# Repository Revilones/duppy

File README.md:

# duppy
This is a test readme
Sense Everything

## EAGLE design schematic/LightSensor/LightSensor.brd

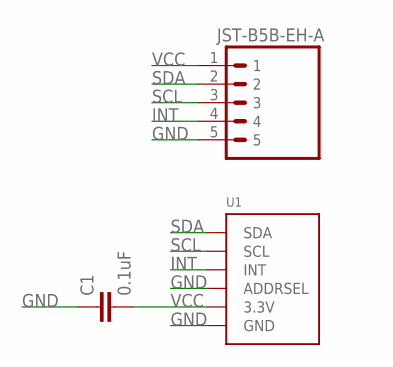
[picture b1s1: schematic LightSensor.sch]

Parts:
C1: 0.1uF; 0603-CAP
U1: LIGHT_TSL2561; TSL2561_FN
U$1: JST-B5B-EH-A; JST-B5B-ED-A

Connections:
GND: C1.1, U1.ADR (ADDRSEL), U1.VSS (GND), U$1.5
INT: U1.INT, U$1.4
SCL: U1.CLK (SCL), U$1.3
SDA: U1.DATA (SDA), U$1.2
VCC: C1.2, U1.VDD (3.3V), U$1.1

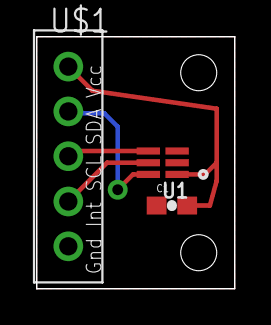
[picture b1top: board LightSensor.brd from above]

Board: 2 copper layers, 11.0 x 14.0 mm, 3 parts (0 on the bottom side), 5 nets.

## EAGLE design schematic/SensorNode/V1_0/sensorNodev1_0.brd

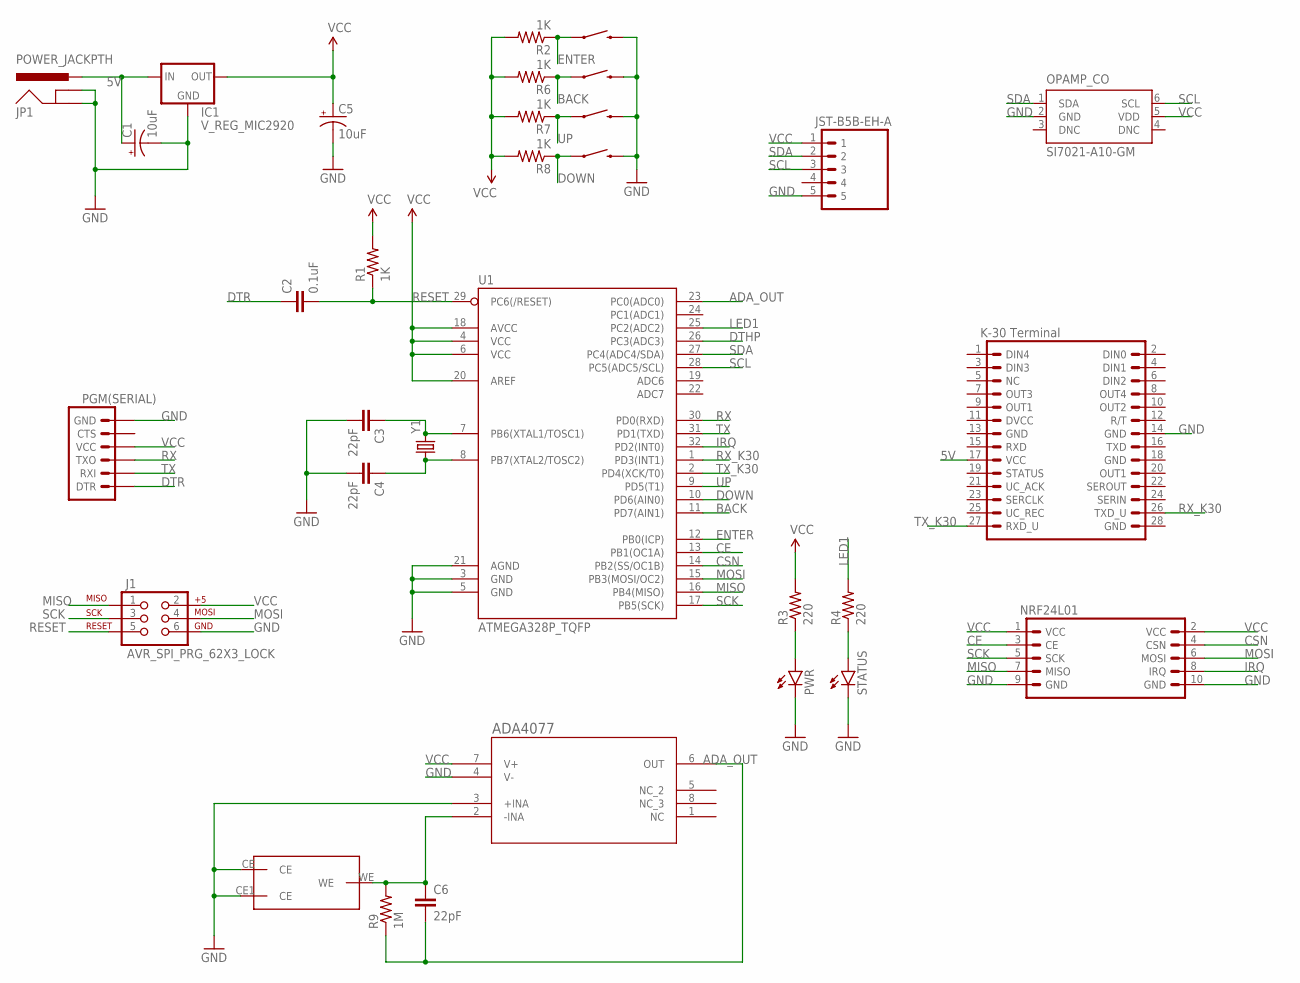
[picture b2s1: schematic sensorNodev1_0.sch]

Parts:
BACK: SWITCH-MOMENTARY-2PTH; TACTILE-PTH
C1, C5: 10uF; CPOL-RADIAL-10UF-25V
C2: 0.1uF; 0603-CAP
C3, C4, C6: 22pF; 0603-CAP
CO2: K-30K-30; K-30
DOWN: SWITCH-MOMENTARY-2PTH; TACTILE-PTH
ENTER: SWITCH-MOMENTARY-2PTH; TACTILE-PTH
IC1: V_REG_MIC2920; SOT223
J1: AVR_SPI_PRG_62X3_LOCK; 2X3_LOCK
JP1: POWER_JACKPTH; POWER_JACK_PTH
OPAMP_CO: SI7021-A10-GM; DFN6-3X3
PGM(SERIAL): ARDUINO_SERIAL_PROGRAMPTH; 1X06
PWR: LED0603; LED-0603
R1, R2, R6, R7, R8: 1K; 0603-RES
R3, R4: 220; 0603-RES
R9: 1M; 0603-RES
SCREEN: JST-B5B-EH-A; JST-B5B-ED-A
STATUS: LED0603; LED-0603
U1: ATMEGA328P_TQFP; TQFP32-08
U2: ADA4077-1ARZ; R_8
U$1: TGS5042A; TGS5042
U$2: NRF24L01
UP: SWITCH-MOMENTARY-2PTH; TACTILE-PTH
Y1: CRYSTALHC49US; HC49US

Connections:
5V: C1.1 (+), CO2.17 (VCC), IC1.1 (IN), JP1.PWR
ADA_OUT: C6.2, R9.1, U1.23 (PC0(ADC0)), U2.6 (OUT)
BACK: BACK.1, R6.1, U1.11 (PD7(AIN1))
CE: U1.13 (PB1(OC1A)), U$2.3 (CE)
CSN: U1.14 (PB2(SS/OC1B)), U$2.4 (CSN)
DOWN: DOWN.1, R8.1, U1.10 (PD6(AIN0))
DTHP: U1.26 (PC3(ADC3))
DTR: C2.1, PGM(SERIAL).1 (DTR)
ENTER: ENTER.1, R2.1, U1.12 (PB0(ICP))
GND: BACK.3 (2), C1.2 (-), C3.2, C4.2, C5.2 (-), CO2.14 (GND), DOWN.3 (2), ENTER.3 (2), IC1.2 (GND), J1.6, JP1.GND, JP1.GNDBREAK, OPAMP_CO.2 (GND), PGM(SERIAL).6 (GND), PWR.C, SCREEN.5, STATUS.C, U1.3 (GND), U1.5 (GND), U1.21 (AGND), U2.3 (+INA), U2.4 (V-), U$1.CE, U$1.CE1 (CE), U$2.9 (GND), U$2.10 (GND), UP.3 (2)
IRQ: U1.32 (PD2(INT0)), U$2.8 (IRQ)
LED1: R4.2, U1.25 (PC2(ADC2))
MISO: J1.1, U1.16 (PB4(MISO)), U$2.7 (MISO)
MOSI: J1.4, U1.15 (PB3(MOSI/OC2)), U$2.6 (MOSI)
unnamed: C3.1, U1.7 (PB6(XTAL1/TOSC1)), Y1.2
unnamed: C4.1, U1.8 (PB7(XTAL2/TOSC2)), Y1.1
unnamed: PWR.A, R3.1
unnamed: R4.1, STATUS.A
unnamed: C6.1, R9.2, U2.2 (-INA), U$1.WE
RESET: C2.2, J1.5, R1.1, U1.29 (PC6(/RESET))
RX: PGM(SERIAL).3 (TXO), U1.30 (PD0(RXD))
RX_K30: CO2.26 (TXD_U), U1.1 (PD3(INT1))
SCK: J1.3, U1.17 (PB5(SCK)), U$2.5 (SCK)
SCL: OPAMP_CO.6 (SCL), SCREEN.3, U1.28 (PC5(ADC5/SCL))
SDA: OPAMP_CO.1 (SDA), SCREEN.2, U1.27 (PC4(ADC4/SDA))
TX: PGM(SERIAL).2 (RXI), U1.31 (PD1(TXD))
TX_K30: CO2.27 (RXD_U), U1.2 (PD4(XCK/T0))
UP: R7.1, U1.9 (PD5(T1)), UP.1
VCC: C5.1 (+), IC1.3 (OUT), J1.2, OPAMP_CO.5 (VDD), PGM(SERIAL).4 (VCC), R1.2, R2.2, R3.2, R6.2, R7.2, R8.2, SCREEN.1, U1.4 (VCC), U1.6 (VCC), U1.18 (AVCC), U1.20 (AREF), U2.7 (V+), U$2.1 (VCC), U$2.2 (VCC)

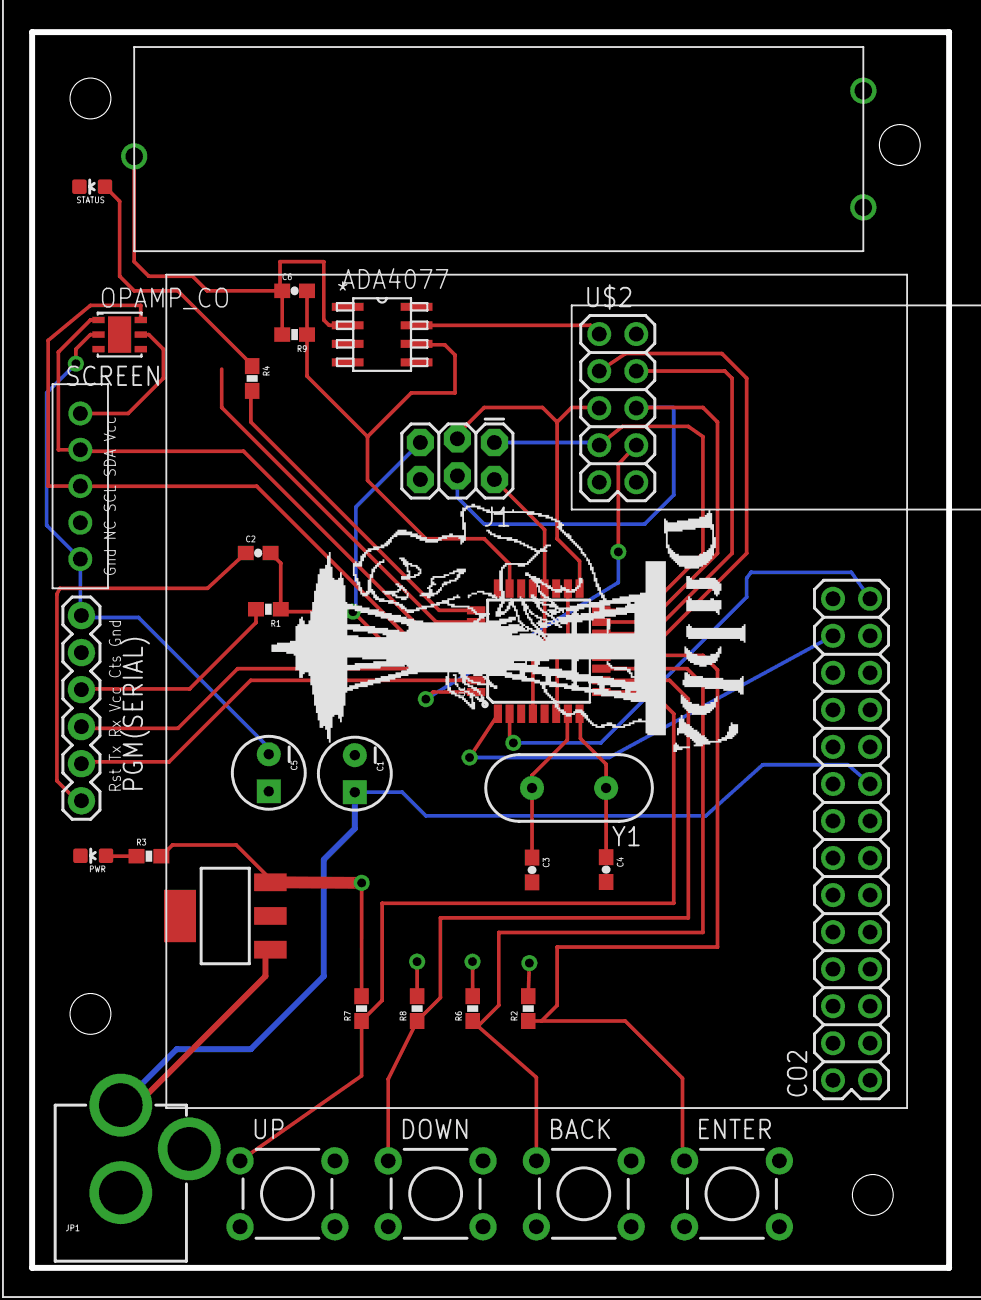
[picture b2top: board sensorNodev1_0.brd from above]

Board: 2 copper layers, 62.9 x 84.7 mm, 34 parts (1 on the bottom side), 28 nets.

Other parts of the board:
U$3: DUPPY_LOGO
U$4: CONTAINER_BOTTOM

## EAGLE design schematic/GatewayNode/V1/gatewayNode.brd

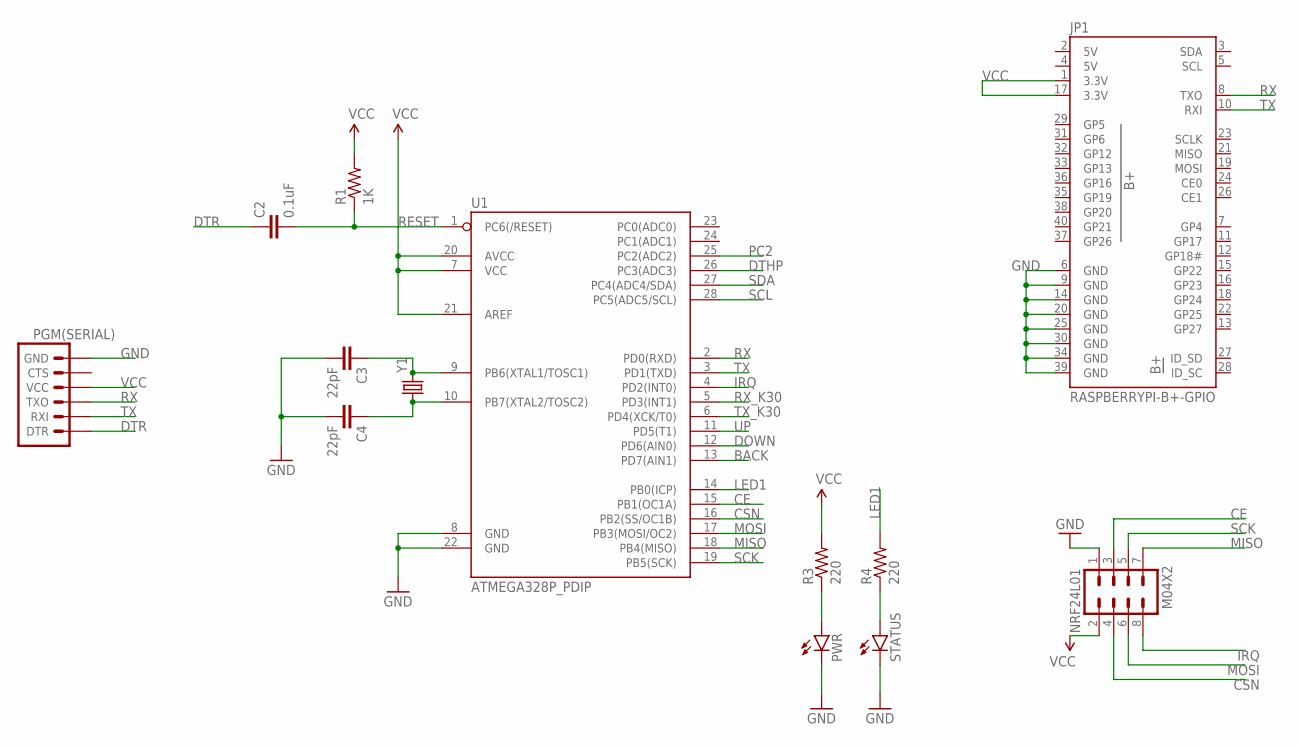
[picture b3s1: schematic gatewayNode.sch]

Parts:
C2: 0.1uF; 0603-CAP
C3, C4: 22pF; 0603-CAP
JP1: RASPBERRYPI-B+-GPIO; 2X20-SHROUDED
NRF24L01: M04X2; 2X4
PGM(SERIAL): ARDUINO_SERIAL_PROGRAMPTH; 1X06
PWR: LED0603; LED-0603
R1: 1K; 0603-RES
R3, R4: 220; 0603-RES
STATUS: LED0603; LED-0603
U1: ATMEGA328P_PDIP; DIL28-3
Y1: CRYSTALHC49US; HC49US

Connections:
5V: JP1.2 (5V), JP1.4 (5V)
BACK: U1.13 (PD7(AIN1))
CE: NRF24L01.3, U1.15 (PB1(OC1A))
CSN: NRF24L01.4, U1.16 (PB2(SS/OC1B))
DOWN: U1.12 (PD6(AIN0))
DTHP: U1.26 (PC3(ADC3))
DTR: C2.1, PGM(SERIAL).1 (DTR)
GND: C3.2, C4.2, JP1.6 (GND), JP1.9 (GND), JP1.14 (GND), JP1.20 (GND), JP1.25 (GND), JP1.30 (GND), JP1.34 (GND), JP1.39 (GND), NRF24L01.1, PGM(SERIAL).6 (GND), PWR.C, STATUS.C, U1.8 (GND), U1.22 (GND)
IRQ: NRF24L01.8, U1.4 (PD2(INT0))
LED1: R4.2, U1.14 (PB0(ICP))
MISO: NRF24L01.7, U1.18 (PB4(MISO))
MOSI: NRF24L01.6, U1.17 (PB3(MOSI/OC2))
unnamed: C3.1, U1.9 (PB6(XTAL1/TOSC1)), Y1.2
unnamed: C4.1, U1.10 (PB7(XTAL2/TOSC2)), Y1.1
unnamed: PWR.A, R3.1
unnamed: R4.1, STATUS.A
PC2: U1.25 (PC2(ADC2))
RESET: C2.2, R1.1, U1.1 (PC6(/RESET))
RX: JP1.8 (TXO), PGM(SERIAL).3 (TXO), U1.2 (PD0(RXD))
RX_K30: U1.5 (PD3(INT1))
SCK: NRF24L01.5, U1.19 (PB5(SCK))
SCL: U1.28 (PC5(ADC5/SCL))
SDA: U1.27 (PC4(ADC4/SDA))
TX: JP1.10 (RXI), PGM(SERIAL).2 (RXI), U1.3 (PD1(TXD))
TX_K30: U1.6 (PD4(XCK/T0))
UP: U1.11 (PD5(T1))
VCC: JP1.1 (3.3V), JP1.17 (3.3V), NRF24L01.2, PGM(SERIAL).4 (VCC), R1.2, R3.2, U1.7 (VCC), U1.20 (AVCC), U1.21 (AREF)

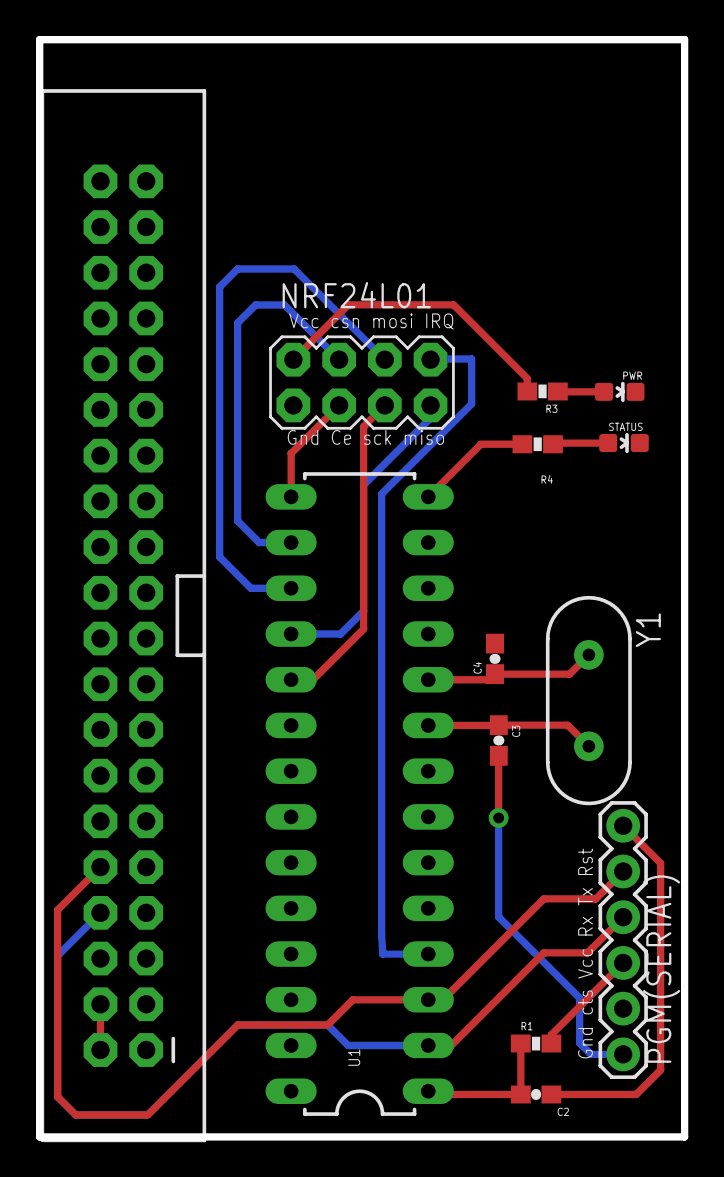
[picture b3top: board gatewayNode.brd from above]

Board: 2 copper layers, 35.8 x 61.0 mm, 13 parts (0 on the bottom side), 18 nets.

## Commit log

2015-03-04 Committing what I have of the web app so far
2015-03-04 Added readme to web app
2015-03-04 Added latest sensor data to sensor API objects
2015-03-06 More work on the webapp, extanding the REST API functionality
2015-03-06 Accidentally commint ctags
2015-03-06 Updated the adapter
2015-03-14 Code drop from wade-dev
    - Added some unittests around API Controller & Node views
    - Refactored dashboard app as single use home use
    Squashed commit of the following:
    commit 65f2a7de7e87a801058c8dd4150065d87b4da12a
    Author: Wade Christie <wade.christie@gmail.com>
    Date: Sat Mar 14 13:52:39 2015 -0700
2015-03-29 Initial Commit of firmware. This includes the following
    Projects:
    o Sensor Node
    o Gateway Node
    o Relay Node
    Libs:
    o MySensors
2015-03-29 Removing unintentional #if
2015-03-29 Adding Libraries
    o AdafruitGFX
    o DigoleSerial
2015-03-29 Switched line endings from dos to unix for DoigoleSerial.h
2015-03-30 Grafted Adafruit_GFX into DigoleSerial
2015-03-30 Adding drawBox with color parameter to Display Lib
2015-03-30 Adding Screen Support for sensor node
2015-04-06 Adding Schematic Directory and SensorNode V2 schematics
2015-04-11 Updated Sensor Node Schematicw
2015-04-12 Added kSeries Lib
2015-04-13 Adding support for Co2 Sensor
2015-04-14 Modified Software Serial to User PinChangeInt Got Gateway and Sensor Node communication working
2015-04-15 Example Code for raspberry pi i2c
2015-04-15 Adding .DS_Store to .gitignore
2015-04-17 Added Co2 Support
2015-04-22 Adding initial enclosure file
2015-04-23 Start of enclosure
2015-04-24 cleaning up .DS_Store files
2015-04-24 adding ._.DS_Store to git ignore
2015-04-24 Code drop from wade-dev
    Squashed commit of the following:
    commit 9dc8e9ff41dc862579d2d551dd2e2aac388acf4a
    Author: Wade Christie <wade.christie@gmail.com>
    Date: Thu Apr 23 20:13:49 2015 -0700
    fixing merge errors
    commit 5b74055143061cc8f5e28dfa5d47cdf79456f29d
2015-05-01 Wrote a couple of django QuerySet views for data analytics
2015-05-03 Updating sensor node and gateway node schematics
2015-05-03 Adding Support for Auto ID
2015-05-03 Updated user interface. Sensor Nodes now have a menu
2015-05-03 Added more to .gitignore
2015-05-08 Updated python package dependencies and fixed fresh install. I also updated the README installtion instructions. Makefile to come.
2015-05-09 Starting work on monitor
2015-05-09 Fix up Merge Issues
2015-05-19 Removing exmapleI2C.py we no longer need it
2015-05-19 Updating enclosure added pcb mounts and lcd mounts
2015-05-19 Updated auto node id generator to determine new node id based on available nodes from Bespin Web Server
2015-05-19 Updated Sensor Node logic to give better performance on user interface
2015-05-23 Updated Enclosure
2015-05-25 Refactored code Added Relay node support for sensor nodes
2015-05-29 Adding Gateway Node schematic
2015-05-29 Adding Sensor Node V3
2015-06-01 Updating bespin adapter to work with https
2015-06-01 Adding data sheet directory
2015-06-01 Adding misc directory... right now it only contains the splash screen
2015-06-10 Adding Gateway enclosure. Updating sensor node enclosure
2015-06-10 o Fixed up adapter to work with https o Cleaned up auto-id system
2015-06-10 Change Website Name from weather center to Duppy Systems
2015-06-15 Removing monitor/migrations
2015-06-16 Adding support for elasticbeanstalk
2015-06-17 Fix Elasticbeanstalk
2015-06-23 Trying to get static files to work
2015-06-25 Remove swagger
2015-06-30 Fix empty response
2015-08-05 Adding new versions of gatewaynode and sensor node
2015-08-06 Adding chart module.
2015-08-13 Fixed up chart so that data from individual sensors can be viewed
2015-08-13 Added Reset option to sensor node firmware
2015-08-14 More work on char
2015-08-15 o Fix bug where Temperature would never change o Increased wait time between sensor readings this really should be modifiable through the web interface
2015-08-17 remove datagen2.py
2015-08-17 Fix and minor improvements on datagen.py
2015-08-24 Allow chart to graph multiple series with different axes
2015-08-30 Adding a base html template for menu
2015-09-06 Adding date range support for sensor data and cleaning up code
2015-09-06 Fixing incorrect setting template configuration
2015-09-06 Modified css to make chart page less ugly
2015-09-18 Chart now identifies sensors by sensor ID and node ID
2015-09-18 Adding SensorTypeView to API
2015-09-27 Improving addToChart function and cleaning up some code
2015-10-13 Adding Blink test program
2015-10-13 Adding Sensor Node V5
2015-10-13 Adding common eagle dru and lib directories
2015-10-13 Removing old splash screen
2015-10-23 Fixed Sensor Node Enclosure o Fixed height to include space for co2 sensor o Added variables for better supportability
2015-10-23 Updating versioning for Enclosure and Schematics so that they can better follow eachother
2015-10-23 Fix blink test program to use standard status led
2015-10-23 Adding datasheets o ADA4077 o Lead Free Solder Paste o Figaro CO Sensor
2015-10-23 Rename from Bespin To Duppy
2015-10-25 More renaming from bespin to duppy
2015-10-27 Updated Webinterface o Added base templates for index o Removed unecissary static files o Added a footer
2015-11-01 o Updated Figaro gas sensor eagle part to reflect version A00 o Fixed opamp circuit in Sensor V5 o Swapped out DHT22 for Si7021
2015-11-02 o Removing old schematic files o Reseting version of Gateway and Sensor node to V1
2015-11-02 Replacing Screen connector with low profile Jst-EH connector
2015-11-02 Renaming files and directories from bespin to Duppy
2015-11-02 Convert to unix line endings
2015-11-02 Renaming variables from bespin to duppy in firmware and adapter
2015-11-02 Accidently moved SensorNode eagle lib to root directory... Moving back
2015-11-04 Refactoring menu code and button code for Sensor Node
2015-11-05 Adding check to make sure sensor exists before registering
2015-11-05 o Fix chart so it only graphs selected sensors o Fix Sensor view so that it doesn't crash the server if there is no data associated with the sensor
2015-11-06 I borked the build!! Adding local variables to fix the commit listed below
    Commit 84a9f3bf1b3e45f7b7d25bb5334c89f98eb9ac2b
2015-11-12 Update to Schematics o Adding light sensor schematic o Added light sensor connector for sensor node o Split part libraries to common and schematic specific
    and surface mount Tmp/Hum module
2015-11-12 Updated enclosure for Sensor Node o Updated size o Added Light Sensor Hole o Changed buttons from top to side
2015-11-30 Patch to MySenssor Lib. o Reboots sensor node after receiving a node id o Adds VGAS Sensor Type
2015-11-30 Upgrade from MySensors 1.4 to 1.5
2015-11-30 Adding #DUPPY definition.
    This will allow us to distinguish duppy specific changes to third
    party libraries.
    This patch also changes the bespinTypes line endings from dos to
    unix
2015-12-10 Adding datasheet for light sensor
2015-12-10 Removing Unneccissary Libraries from MySensors 1.5
2015-12-10 Updating firmware to support new hardware o light sensor o CO Sensor o Refactored Sensors display to be more genric

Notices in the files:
parts and their libraries:
SparkFun-Capacitors: Licensing: Creative Commons ShareAlike 4.0 International - https://creativecommons.org/licenses/by-sa/4.0
